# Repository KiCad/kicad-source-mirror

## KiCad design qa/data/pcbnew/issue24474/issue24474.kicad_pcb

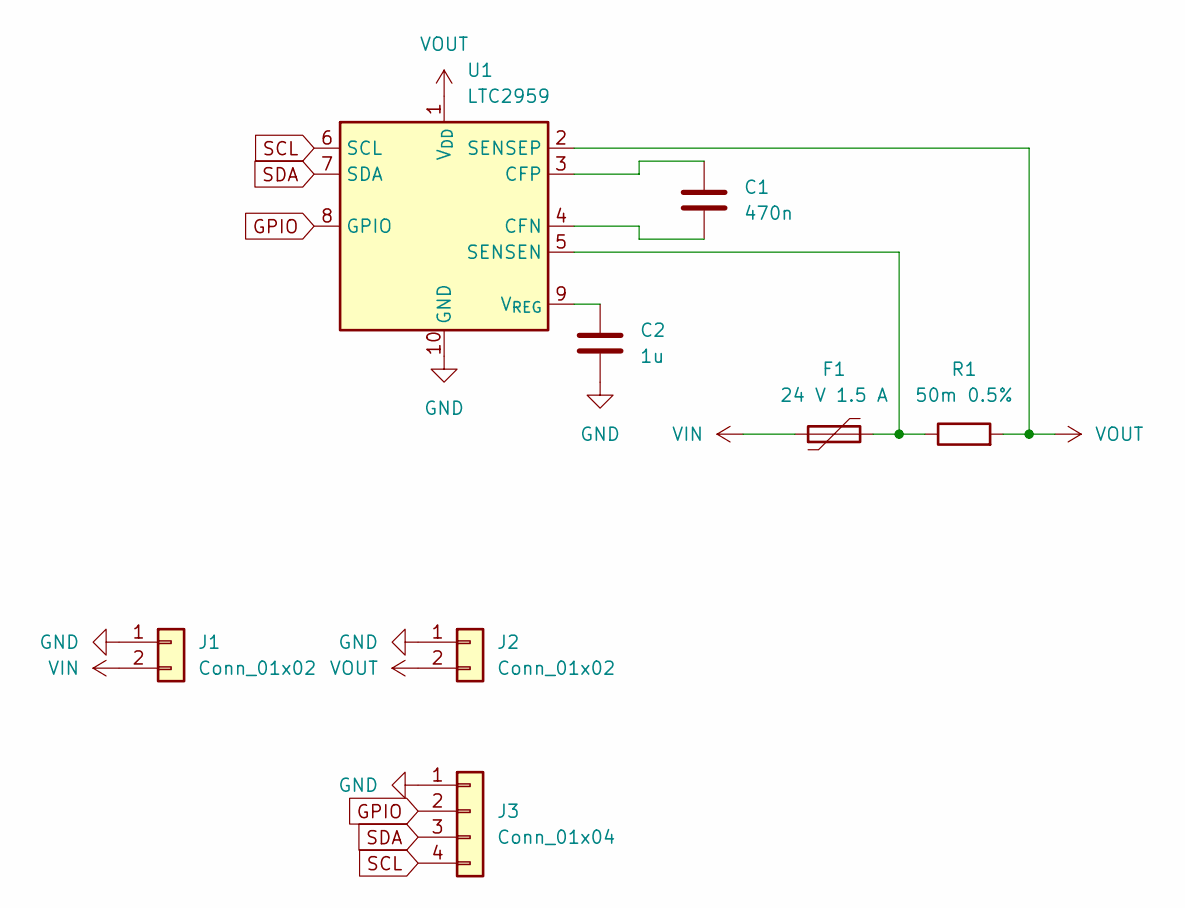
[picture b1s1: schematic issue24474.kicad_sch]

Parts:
C1: 470n; C_0402_1005Metric
C2: 1u; C_0402_1005Metric
F1: 24 V 1.5 A; Fuse_1812_4532Metric_Pad1.30x3.40mm_HandSolder
J1, J2: Conn_01x02; JST_XH_B2B-XH-A_1x02_P2.50mm_Vertical
J3: Conn_01x04; JST_XH_B4B-XH-A_1x04_P2.50mm_Vertical
R1: 50m 0.5%; R_1206_3216Metric_Pad1.30x1.75mm_HandSolder
U1: LTC2959; DFN-10-1EP_2x3mm_P0.5mm_EP0.64x2.4mm

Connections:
GND: C2.2, J1.1, J2.1, J3.1, U1.10 (GND)
GPIO: J3.2, U1.8 (GPIO)
unnamed: C1.2, U1.4 (CFN)
unnamed: C1.1, U1.3 (CFP)
unnamed: F1.2, R1.1, U1.5 (SENSEN)
unnamed: C2.1, U1.9 (V_{REG})
SCL: J3.4, U1.6 (SCL)
SDA: J3.3, U1.7 (SDA)
VIN: F1.1, J1.2
VOUT: J2.2, R1.2, U1.1 (V_{DD}), U1.2 (SENSEP)

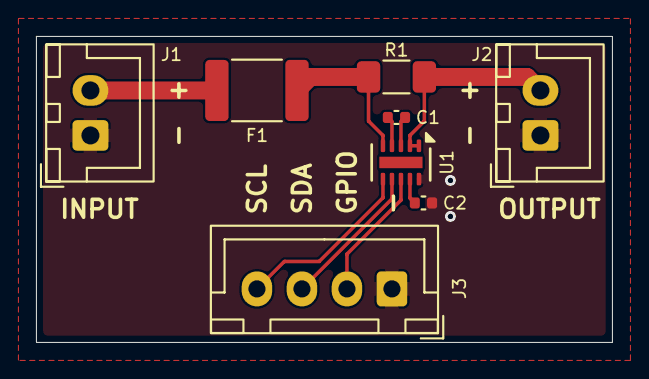
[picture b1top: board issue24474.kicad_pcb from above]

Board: 2 copper layers, 32.0 x 17.0 mm, 8 parts (0 on the bottom side), 10 nets.
